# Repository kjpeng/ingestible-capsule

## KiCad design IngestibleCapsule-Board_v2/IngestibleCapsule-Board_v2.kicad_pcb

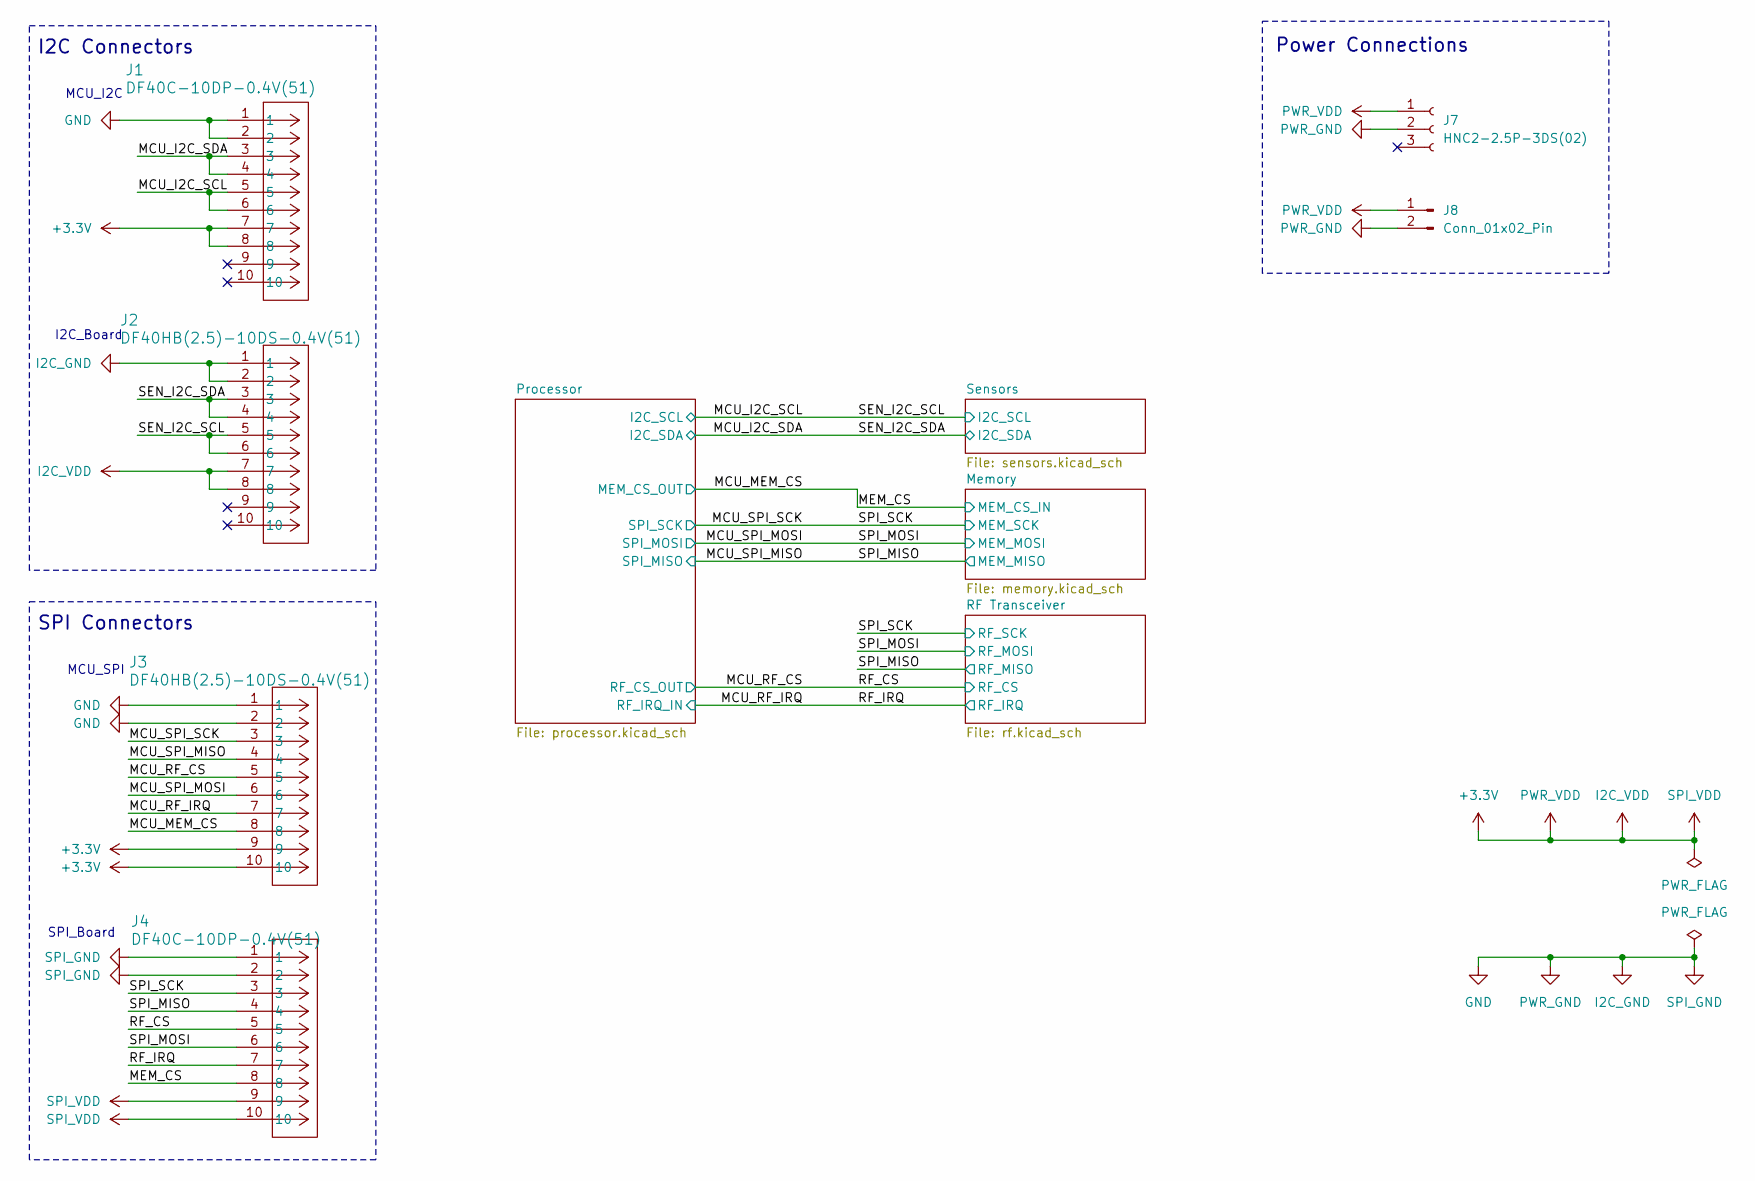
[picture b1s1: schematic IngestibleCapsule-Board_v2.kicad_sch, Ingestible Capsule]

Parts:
J1, J4: DF40C-10DP-0.4V(51)
J2, J3: DF40HB(2.5)-10DS-0.4V(51)
J7: HNC2-2.5P-3DS(02)
J8: Conn_01x02_Pin; PinSocket_1x02_P2.54mm_Vertical

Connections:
+3.3V: J1.7, J1.8, J2.7, J2.8, J3.9, J3.10, J4.9, J4.10, J7.1, J8.1; also elsewhere on the board
/MCU_I2C_SCL: J1.5, J1.6, J2.5, J2.6; also elsewhere on the board
/MCU_I2C_SDA: J1.3, J1.4, J2.3, J2.4; also elsewhere on the board
/MCU_MEM_CS: J3.8, J4.8; also elsewhere on the board
/MCU_RF_CS: J3.5, J4.5; also elsewhere on the board
/MCU_RF_IRQ: J3.7, J4.7; also elsewhere on the board
/MCU_SPI_MISO: J3.4, J4.4; also elsewhere on the board
/MCU_SPI_MOSI: J3.6, J4.6; also elsewhere on the board
/MCU_SPI_SCK: J3.3, J4.3; also elsewhere on the board
GND: J1.1, J1.2, J2.1, J2.2, J3.1, J3.2, J4.1, J4.2, J7.2, J8.2; also elsewhere on the board

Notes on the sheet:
MCU_I2C
I2C_Board
MCU_SPI
SPI_Board
SPI Connectors
I2C Connectors
Power Connections

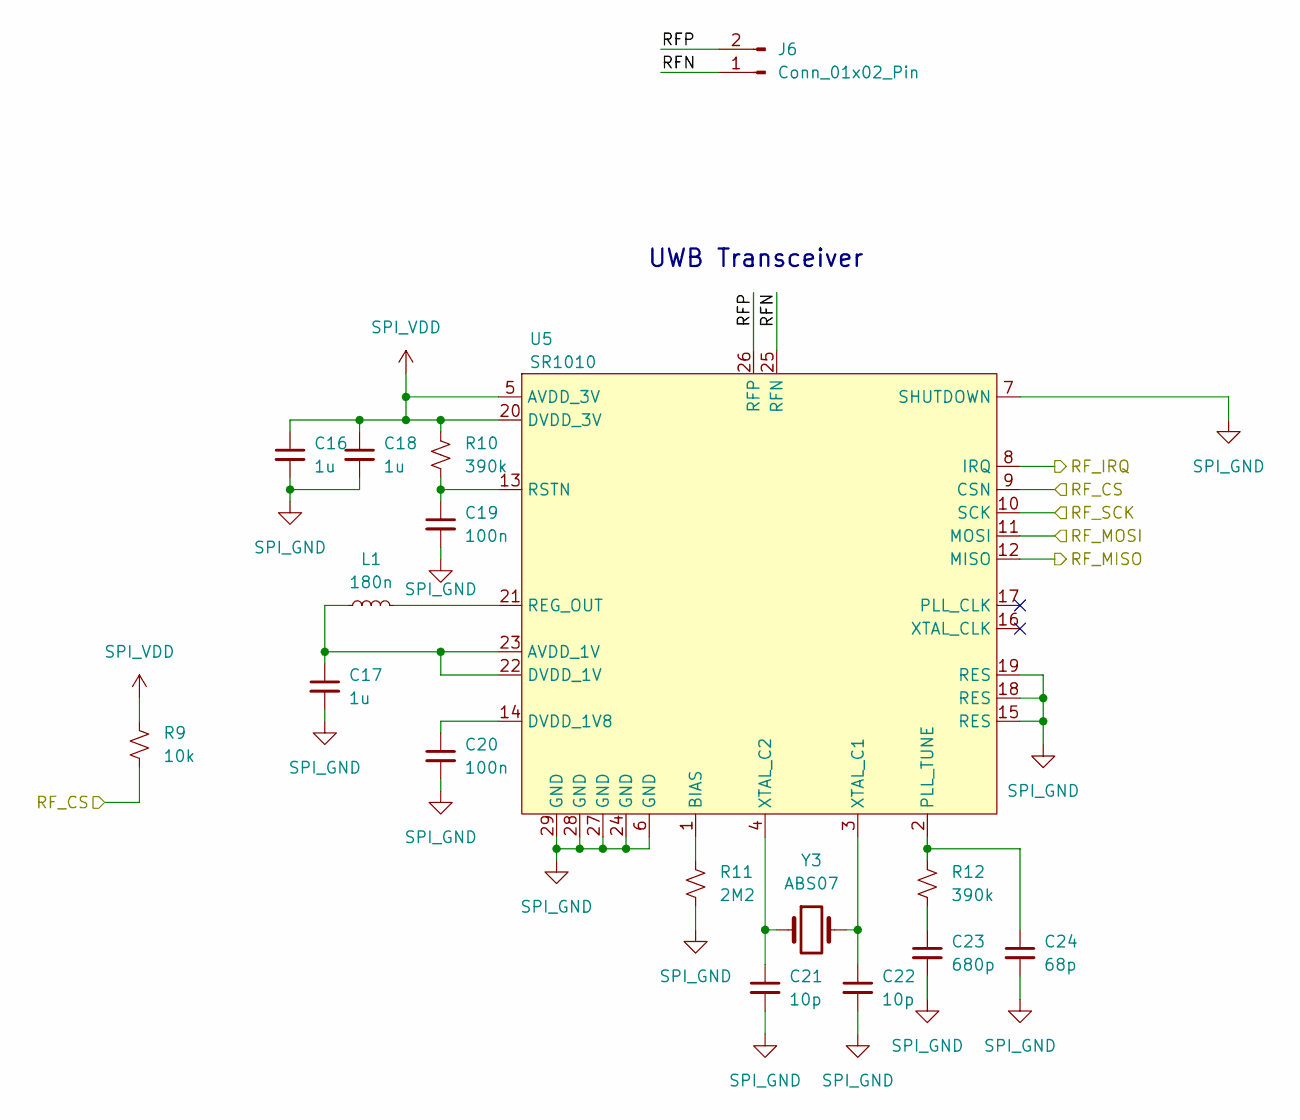
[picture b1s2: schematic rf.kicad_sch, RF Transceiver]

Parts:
C16, C17, C18: 1u; C_0402_1005Metric
C19, C20: 100n; C_0402_1005Metric
C21, C22: 10p; C_0402_1005Metric
C23: 680p; C_0402_1005Metric
C24: 68p; C_0402_1005Metric
J6: Conn_01x02_Pin; BM02BSRSSTBLFSN
L1: 180n; L_0402_1005Metric
R9: 10k; R_0402_1005Metric
R10, R12: 390k; R_0402_1005Metric
R11: 2M2; R_0603_1608Metric
U5: SR1010
Y3: ABS07; ABS07-120-32.768KHZ-T

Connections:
+3.3V: C16.1, C18.1, R9.1, R10.1, U5.5 (AVDD_3V), U5.20 (DVDD_3V); also elsewhere on the board
/MCU_RF_CS: R9.2, U5.9 (CSN); also elsewhere on the board
/MCU_RF_IRQ: U5.8 (IRQ); also elsewhere on the board
/MCU_SPI_MISO: U5.12 (MISO); also elsewhere on the board
/MCU_SPI_MOSI: U5.11 (MOSI); also elsewhere on the board
/MCU_SPI_SCK: U5.10 (SCK); also elsewhere on the board
/RF Transceiver/RFN: J6.1, U5.25 (RFN)
/RF Transceiver/RFP: J6.2, U5.26 (RFP)
GND: C16.2, C17.2, C18.2, C19.2, C20.2, C21.2, C22.2, C23.2, C24.2, R11.2, U5.6 (GND), U5.7 (SHUTDOWN), U5.15 (RES), U5.18 (RES), U5.19 (RES), U5.24 (GND), U5.27 (GND), U5.28 (GND), U5.29 (GND); also elsewhere on the board
unnamed: C23.1, R12.2
unnamed: C17.1, L1.1, U5.22 (DVDD_1V), U5.23 (AVDD_1V)
unnamed: R11.1, U5.1 (BIAS)
unnamed: C20.1, U5.14 (DVDD_1V8)
unnamed: C24.1, R12.1, U5.2 (PLL_TUNE)
unnamed: L1.2, U5.21 (REG_OUT)
unnamed: C19.1, R10.2, U5.13 (RSTN)
unnamed: C22.1, U5.3 (XTAL_C1), Y3.2
unnamed: C21.1, U5.4 (XTAL_C2), Y3.1

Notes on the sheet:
UWB Transceiver

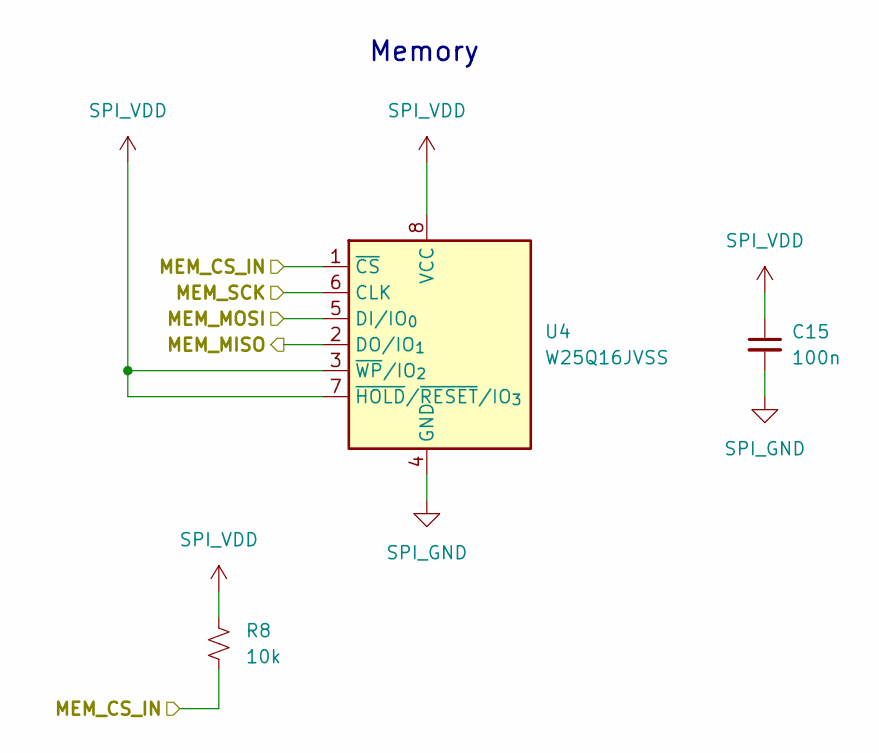
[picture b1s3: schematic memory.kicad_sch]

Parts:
C15: 100n; C_0402_1005Metric
R8: 10k; R_0402_1005Metric
U4: W25Q16JVSS; SOIC-8_5.3x5.3mm_P1.27mm

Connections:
+3.3V: C15.1, R8.1, U4.3 (~WP/IO_{2}), U4.7 (~HOLD/~RESET/IO_{3}), U4.8 (VCC); also elsewhere on the board
/MCU_MEM_CS: R8.2, U4.1 (~CS); also elsewhere on the board
/MCU_SPI_MISO: U4.2 (DO/IO_{1}); also elsewhere on the board
/MCU_SPI_MOSI: U4.5 (DI/IO_{0}); also elsewhere on the board
/MCU_SPI_SCK: U4.6 (CLK); also elsewhere on the board
GND: C15.2, U4.4 (GND); also elsewhere on the board

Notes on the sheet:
Memory

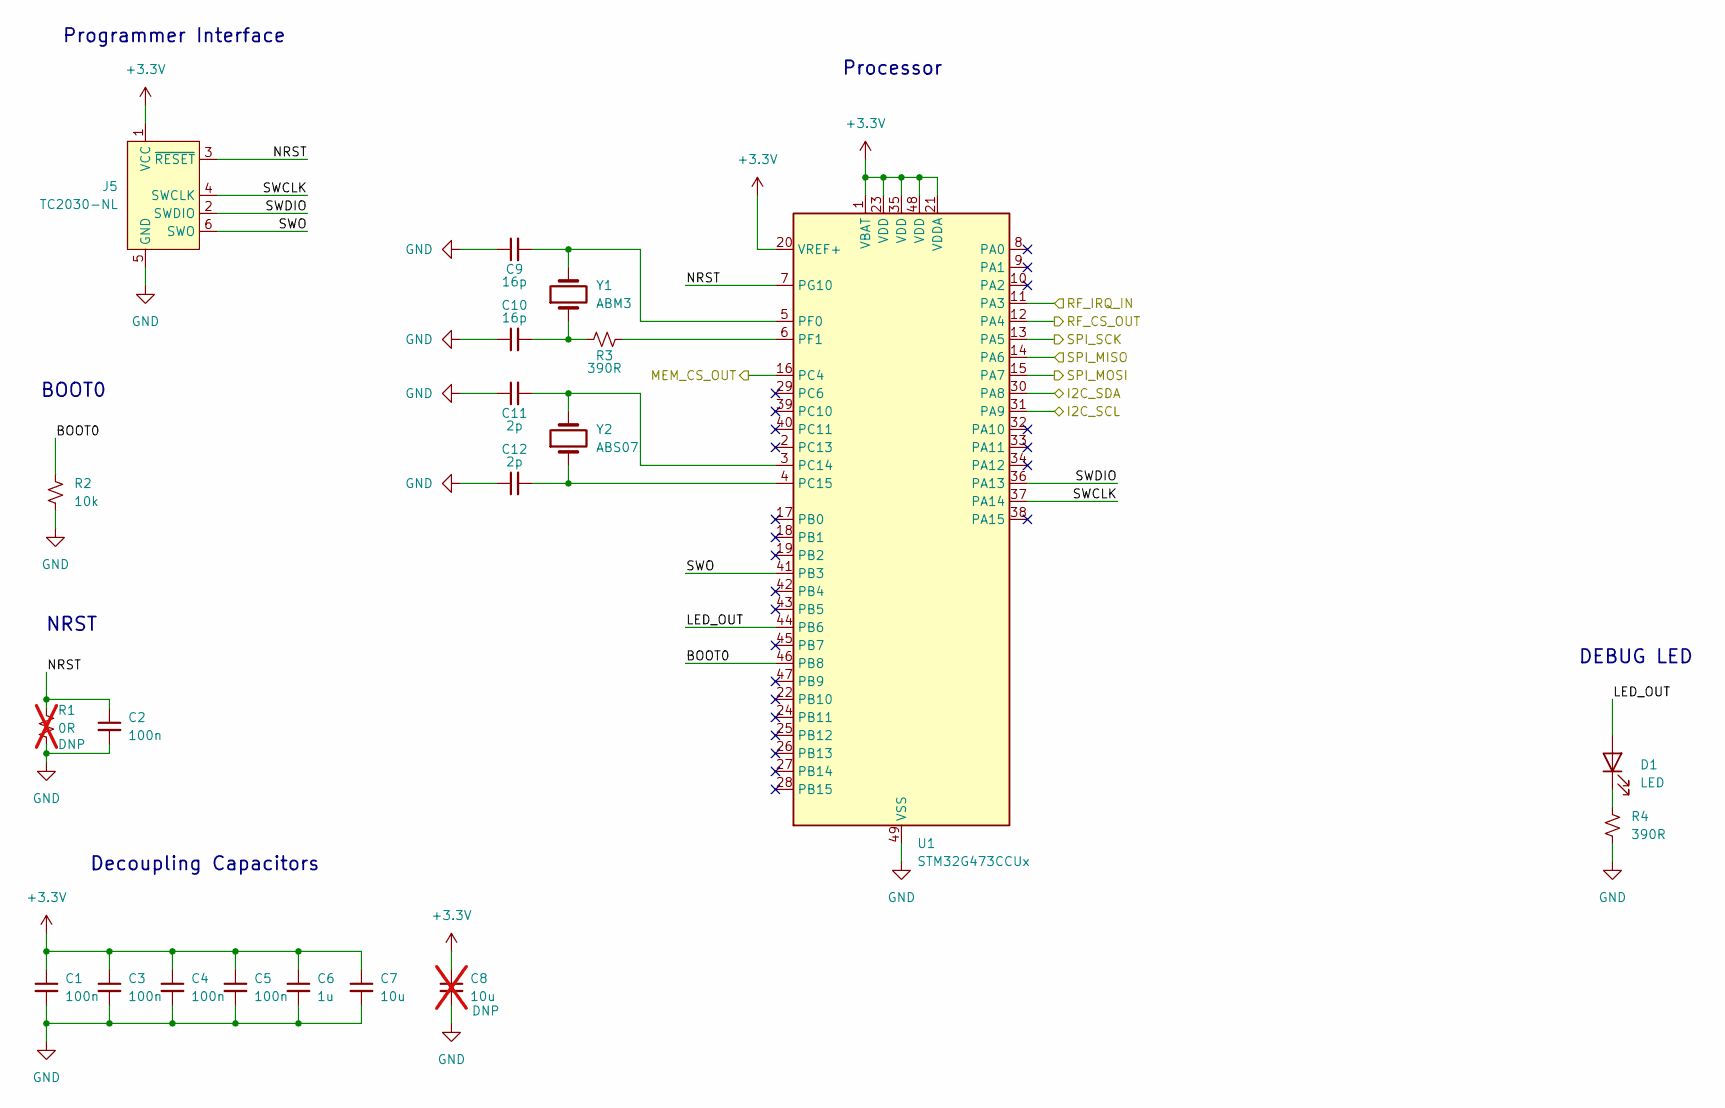
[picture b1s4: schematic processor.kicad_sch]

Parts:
C1, C2, C3, C4, C5: 100n; C_0402_1005Metric
C6: 1u; C_0402_1005Metric
C7: 10u; C_0603_1608Metric
C8: 10u; C_0603_1608Metric; not fitted
C9, C10: 16p; C_0402_1005Metric
C11, C12: 2p; C_0402_1005Metric
D1: LED; LED_0402_1005Metric
J5: TC2030-NL; Tag-Connect_TC2030-IDC-NL_2x03_P1.27mm_Vertical
R1: 0R; R_0402_1005Metric; not fitted
R2: 10k; R_0402_1005Metric
R3, R4: 390R; R_0402_1005Metric
U1: STM32G473CCUx; QFN-48-1EP_7x7mm_P0.5mm_EP5.6x5.6mm
Y1: ABM3; ABM3-48.000MHZ-B2-T
Y2: ABS07; ABS07-120-32.768KHZ-T

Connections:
+3.3V: C1.1, C3.1, C4.1, C5.1, C6.1, C7.1, C8.1, J5.1 (VCC), U1.1 (VBAT), U1.20 (VREF+), U1.21 (VDDA), U1.23 (VDD), U1.35 (VDD), U1.48 (VDD); also elsewhere on the board
/MCU_I2C_SCL: U1.31 (PA9); also elsewhere on the board
/MCU_I2C_SDA: U1.30 (PA8); also elsewhere on the board
/MCU_MEM_CS: U1.16 (PC4); also elsewhere on the board
/MCU_RF_CS: U1.12 (PA4); also elsewhere on the board
/MCU_RF_IRQ: U1.11 (PA3); also elsewhere on the board
/MCU_SPI_MISO: U1.14 (PA6); also elsewhere on the board
/MCU_SPI_MOSI: U1.15 (PA7); also elsewhere on the board
/MCU_SPI_SCK: U1.13 (PA5); also elsewhere on the board
/Processor/BOOT0: R2.1, U1.46 (PB8)
/Processor/LED_OUT: D1.2 (A), U1.44 (PB6)
/Processor/NRST: C2.1, J5.3 (~RESET), R1.1, U1.7 (PG10)
/Processor/SWCLK: J5.4 (SWCLK), U1.37 (PA14)
/Processor/SWDIO: J5.2 (SWDIO), U1.36 (PA13)
/Processor/SWO: J5.6 (SWO), U1.41 (PB3)
GND: C1.2, C2.2, C3.2, C4.2, C5.2, C6.2, C7.2, C8.2, C9.1, C10.1, C11.1, C12.1, J5.5 (GND), R1.2, R2.2, R4.2, U1.49 (VSS); also elsewhere on the board
unnamed: C10.2, R3.1, Y1.1
unnamed: D1.1 (K), R4.1
unnamed: C11.2, U1.3 (PC14), Y2.2
unnamed: C12.2, U1.4 (PC15), Y2.1
unnamed: C9.2, U1.5 (PF0), Y1.2
unnamed: R3.2, U1.6 (PF1)

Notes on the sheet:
Programmer Interface
Decoupling Capacitors
BOOT0
NRST
Processor
DEBUG LED

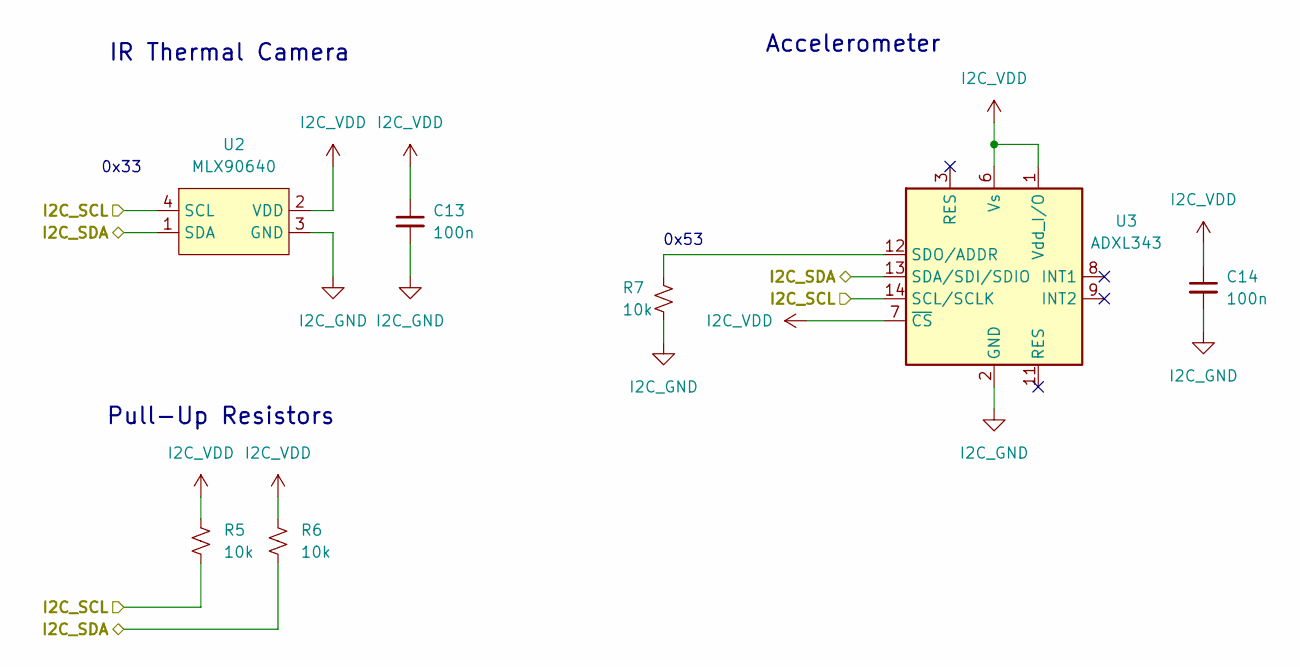
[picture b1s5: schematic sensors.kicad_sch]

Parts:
C13, C14: 100n; C_0402_1005Metric
R5, R6, R7: 10k; R_0402_1005Metric
U2: MLX90640
U3: ADXL343; LGA-14_3x5mm_P0.8mm_LayoutBorder1x6y

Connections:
+3.3V: C13.1, C14.1, R5.1, R6.1, U2.2 (VDD), U3.1 (Vdd_I/O), U3.6 (Vs), U3.7 (~CS); also elsewhere on the board
/MCU_I2C_SCL: R5.2, U2.4 (SCL), U3.14 (SCL/SCLK); also elsewhere on the board
/MCU_I2C_SDA: R6.2, U2.1 (SDA), U3.13 (SDA/SDI/SDIO); also elsewhere on the board
GND: C13.2, C14.2, R7.1, U2.3 (GND), U3.2 (GND), U3.4 (GND), U3.5 (GND); also elsewhere on the board
unnamed: R7.2, U3.12 (SDO/ADDR)

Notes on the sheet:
0x53
IR Thermal Camera
Accelerometer
0x33
Pull-Up Resistors

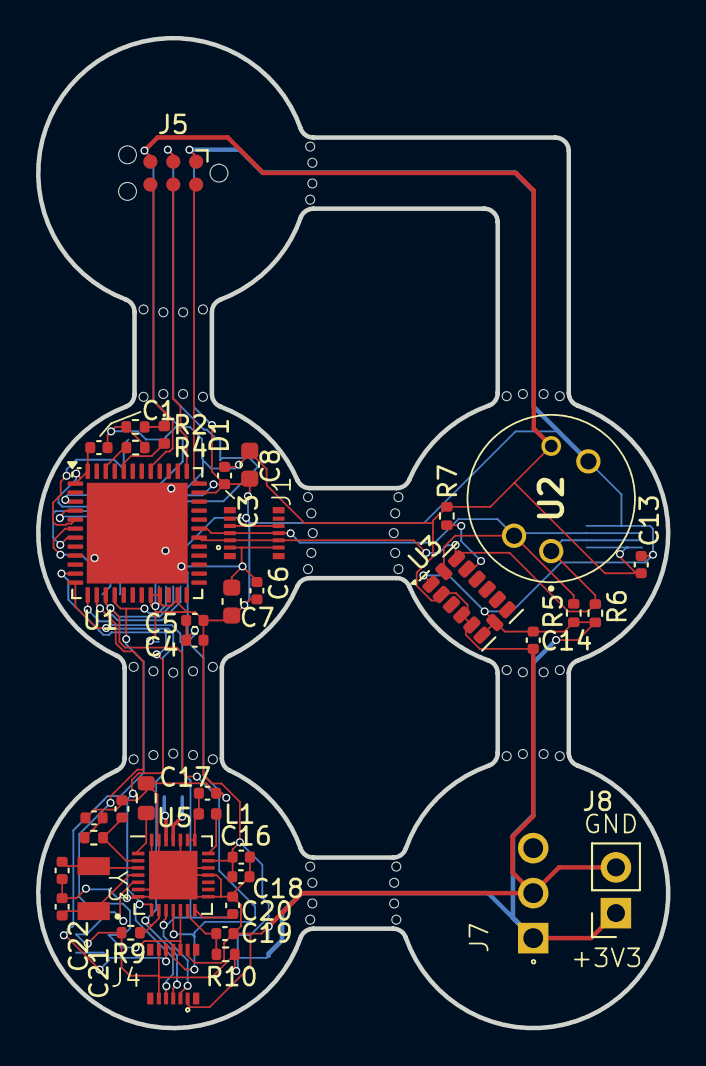
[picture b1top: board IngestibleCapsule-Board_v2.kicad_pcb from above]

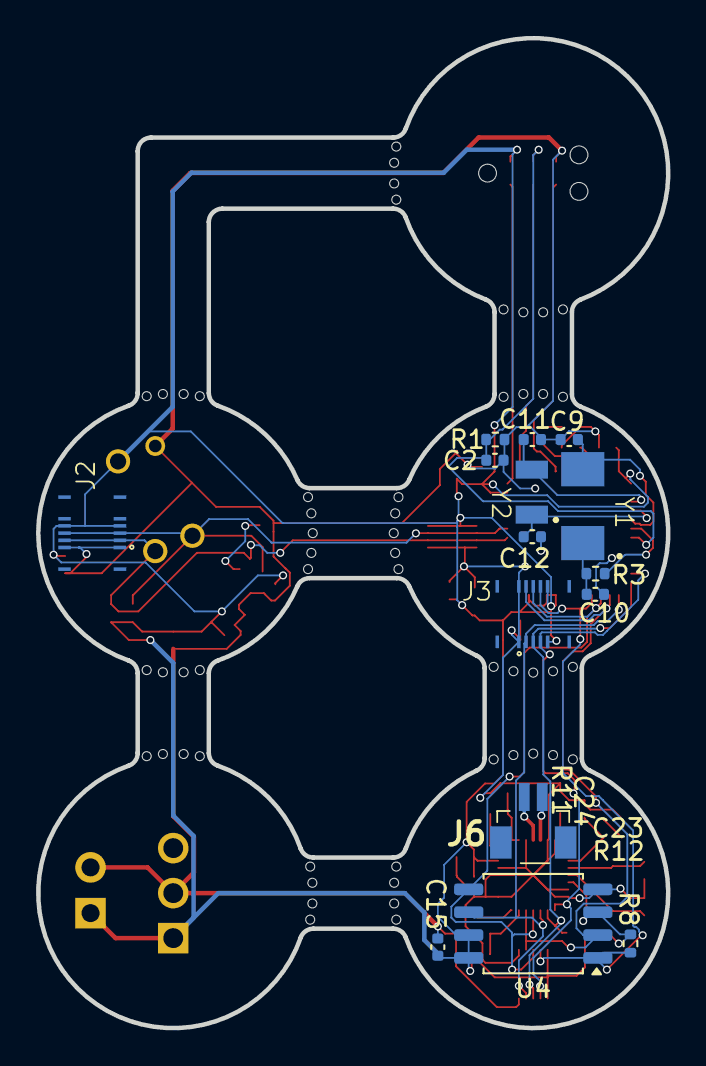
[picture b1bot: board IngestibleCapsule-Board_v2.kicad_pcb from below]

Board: 2 copper layers, 35.0 x 55.0 mm, 66 parts (15 on the bottom side), 34 nets.

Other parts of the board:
i2c_2_2, i2c_2_2#2: VAL**; i2c_2_2
prog_3_2, prog_3_2#2: VAL**; prog_3_2
pwr_4_2, pwr_4_2#2, pwr_4_2#3, pwr_4_2#4, pwr_4_2#5, pwr_4_2#6: VAL**; pwr_4_2
spi_4_2, spi_4_2#2: VAL**; spi_4_2

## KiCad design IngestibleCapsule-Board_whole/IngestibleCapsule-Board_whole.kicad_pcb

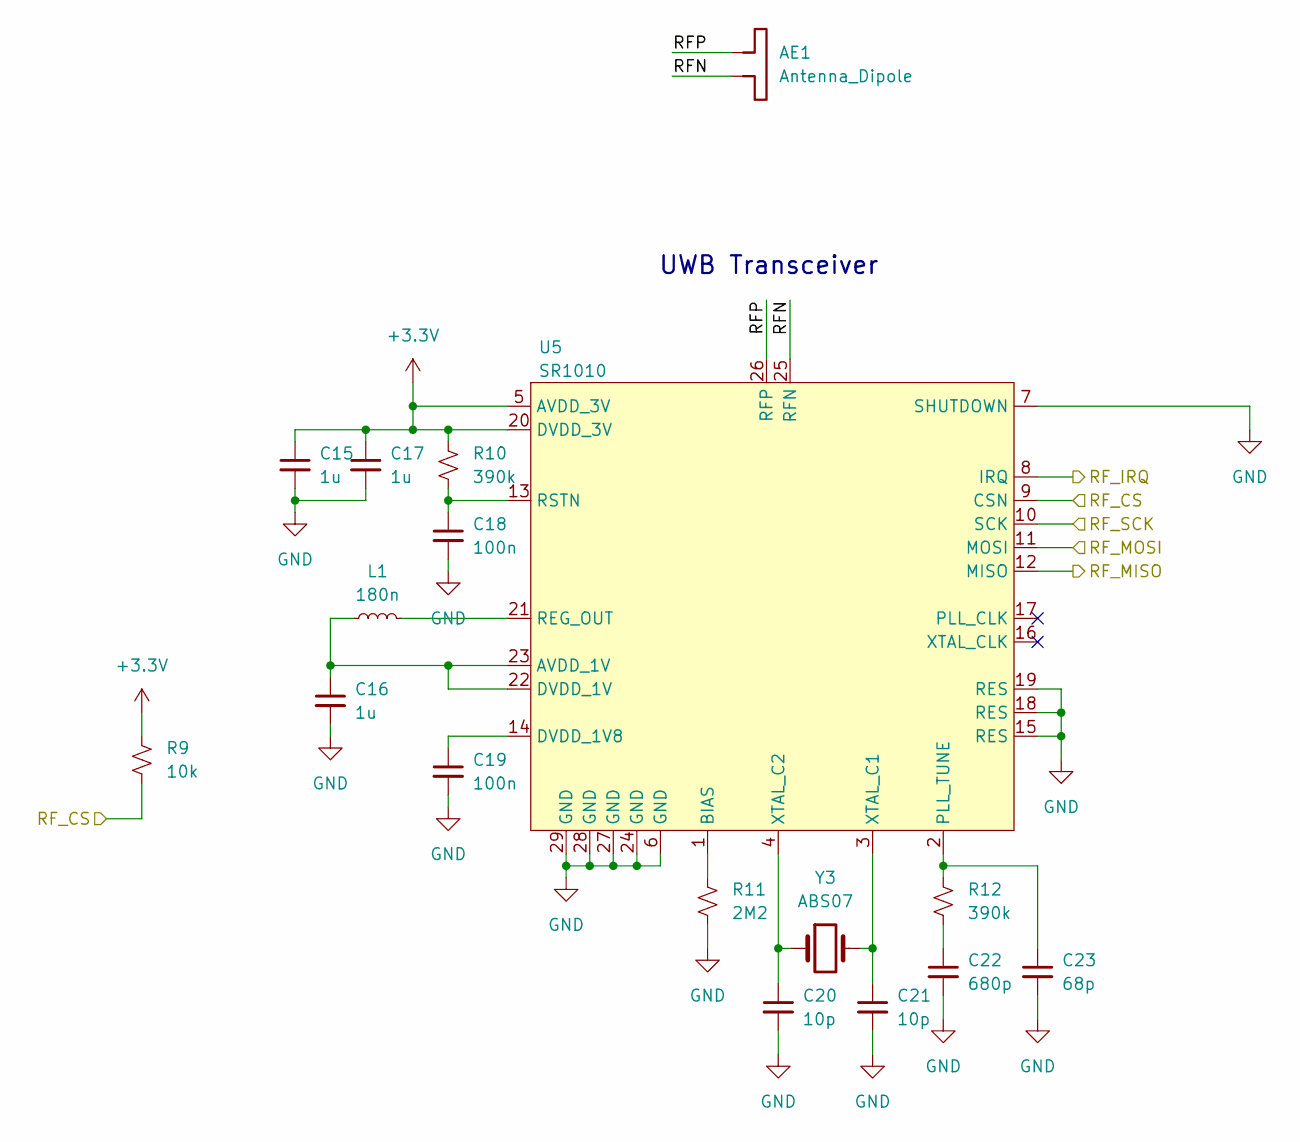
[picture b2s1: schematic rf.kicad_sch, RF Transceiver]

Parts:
AE1: Antenna_Dipole; Dipole Antenna
C15, C16, C17: 1u; C_0402_1005Metric
C18, C19: 100n; C_0402_1005Metric
C20, C21: 10p; C_0402_1005Metric
C22: 680p; C_0402_1005Metric
C23: 68p; C_0402_1005Metric
L1: 180n; L_0402_1005Metric
R9: 10k; R_0402_1005Metric
R10, R12: 390k; R_0402_1005Metric
R11: 2M2; R_0603_1608Metric
U5: SR1010; QFN-28-1EP_4x4mm_P0.4mm_EP2.7x2.7mm
Y3: ABS07; ABS07-120-32.768KHZ-T

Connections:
+3.3V: C15.1, C17.1, R9.1, R10.1, U5.5 (AVDD_3V), U5.20 (DVDD_3V); also elsewhere on the board
/Memory/MEM_MISO: U5.12 (MISO); also elsewhere on the board
/Memory/MEM_MOSI: U5.11 (MOSI); also elsewhere on the board
/Memory/MEM_SCK: U5.10 (SCK); also elsewhere on the board
/Processor/RF_CS_OUT: R9.2, U5.9 (CSN); also elsewhere on the board
/Processor/RF_IRQ_IN: U5.8 (IRQ); also elsewhere on the board
/RF Transceiver/RFN: AE1.2, U5.25 (RFN)
/RF Transceiver/RFP: AE1.1, U5.26 (RFP)
GND: C15.2, C16.2, C17.2, C18.2, C19.2, C20.2, C21.2, C22.2, C23.2, R11.2, U5.6 (GND), U5.7 (SHUTDOWN), U5.15 (RES), U5.18 (RES), U5.19 (RES), U5.24 (GND), U5.27 (GND), U5.28 (GND), U5.29 (GND); also elsewhere on the board
unnamed: C22.1, R12.2
unnamed: C16.1, L1.1, U5.22 (DVDD_1V), U5.23 (AVDD_1V)
unnamed: R11.1, U5.1 (BIAS)
unnamed: C19.1, U5.14 (DVDD_1V8)
unnamed: C23.1, R12.1, U5.2 (PLL_TUNE)
unnamed: L1.2, U5.21 (REG_OUT)
unnamed: C18.1, R10.2, U5.13 (RSTN)
unnamed: C21.1, U5.3 (XTAL_C1), Y3.2
unnamed: C20.1, U5.4 (XTAL_C2), Y3.1

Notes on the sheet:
UWB Transceiver

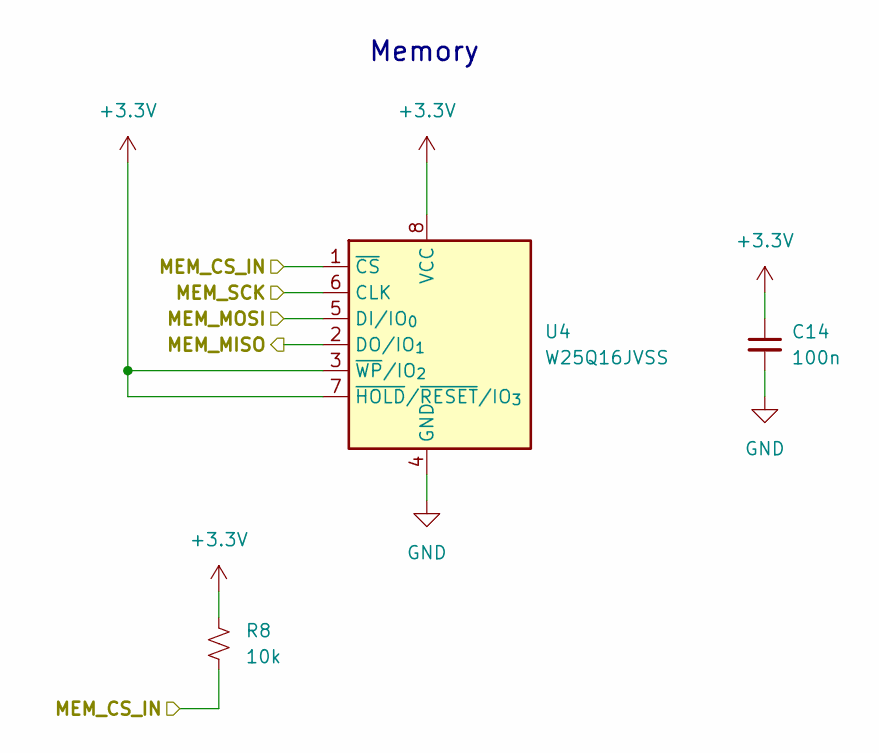
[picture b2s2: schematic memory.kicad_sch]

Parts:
C14: 100n; C_0402_1005Metric
R8: 10k; R_0402_1005Metric
U4: W25Q16JVSS; SOIC-8_5.3x5.3mm_P1.27mm

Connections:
+3.3V: C14.1, R8.1, U4.3 (~WP/IO_{2}), U4.7 (~HOLD/~RESET/IO_{3}), U4.8 (VCC); also elsewhere on the board
/Memory/MEM_CS_IN: R8.2, U4.1 (~CS); also elsewhere on the board
/Memory/MEM_MISO: U4.2 (DO/IO_{1}); also elsewhere on the board
/Memory/MEM_MOSI: U4.5 (DI/IO_{0}); also elsewhere on the board
/Memory/MEM_SCK: U4.6 (CLK); also elsewhere on the board
GND: C14.2, U4.4 (GND); also elsewhere on the board

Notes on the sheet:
Memory

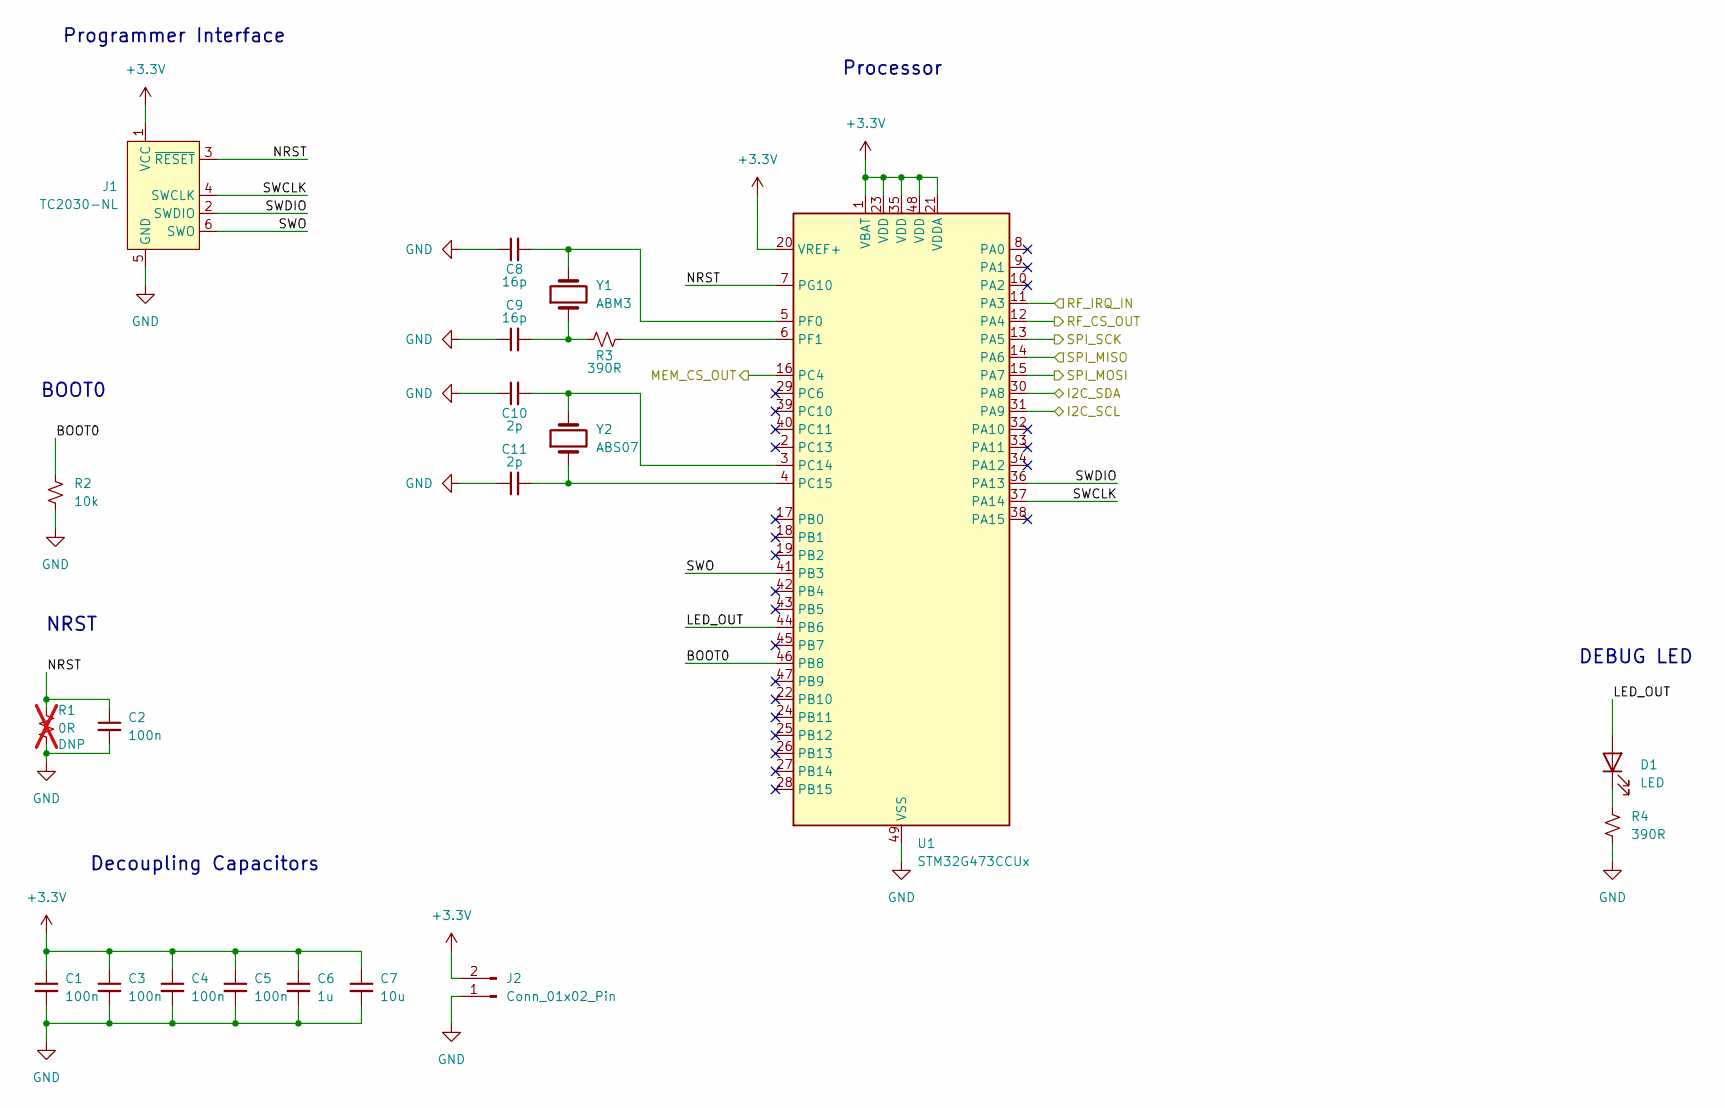
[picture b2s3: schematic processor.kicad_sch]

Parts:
C1, C2, C3, C4, C5: 100n; C_0402_1005Metric
C6: 1u; C_0402_1005Metric
C7: 10u; C_0603_1608Metric
C8, C9: 16p; C_0402_1005Metric
C10, C11: 2p; C_0402_1005Metric
D1: LED; LED_0402_1005Metric
J1: TC2030-NL; Tag-Connect_TC2030-IDC-NL_2x03_P1.27mm_Vertical
J2: Conn_01x02_Pin; PinHeader_1x02_P2.54mm_Vertical
R1: 0R; R_0402_1005Metric; not fitted
R2: 10k; R_0402_1005Metric
R3, R4: 390R; R_0402_1005Metric
U1: STM32G473CCUx; QFN-48-1EP_7x7mm_P0.5mm_EP5.6x5.6mm
Y1: ABM3; ABM3-48.000MHZ-B2-T
Y2: ABS07; ABS07-120-32.768KHZ-T

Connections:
+3.3V: C1.1, C3.1, C4.1, C5.1, C6.1, C7.1, J1.1 (VCC), J2.2, U1.1 (VBAT), U1.20 (VREF+), U1.21 (VDDA), U1.23 (VDD), U1.35 (VDD), U1.48 (VDD); also elsewhere on the board
/Memory/MEM_CS_IN: U1.16 (PC4); also elsewhere on the board
/Memory/MEM_MISO: U1.14 (PA6); also elsewhere on the board
/Memory/MEM_MOSI: U1.15 (PA7); also elsewhere on the board
/Memory/MEM_SCK: U1.13 (PA5); also elsewhere on the board
/Processor/BOOT0: R2.1, U1.46 (PB8)
/Processor/I2C_SCL: U1.31 (PA9); also elsewhere on the board
/Processor/I2C_SDA: U1.30 (PA8); also elsewhere on the board
/Processor/LED_OUT: D1.2 (A), U1.44 (PB6)
/Processor/NRST: C2.1, J1.3 (~RESET), R1.1, U1.7 (PG10)
/Processor/RF_CS_OUT: U1.12 (PA4); also elsewhere on the board
/Processor/RF_IRQ_IN: U1.11 (PA3); also elsewhere on the board
/Processor/SWCLK: J1.4 (SWCLK), U1.37 (PA14)
/Processor/SWDIO: J1.2 (SWDIO), U1.36 (PA13)
/Processor/SWO: J1.6 (SWO), U1.41 (PB3)
GND: C1.2, C2.2, C3.2, C4.2, C5.2, C6.2, C7.2, C8.1, C9.1, C10.1, C11.1, J1.5 (GND), J2.1, R1.2, R2.2, R4.2, U1.49 (VSS); also elsewhere on the board
unnamed: C9.2, R3.1, Y1.1
unnamed: D1.1 (K), R4.1
unnamed: C10.2, U1.3 (PC14), Y2.2
unnamed: C11.2, U1.4 (PC15), Y2.1
unnamed: C8.2, U1.5 (PF0), Y1.2
unnamed: R3.2, U1.6 (PF1)

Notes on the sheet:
Programmer Interface
Decoupling Capacitors
BOOT0
NRST
Processor
DEBUG LED

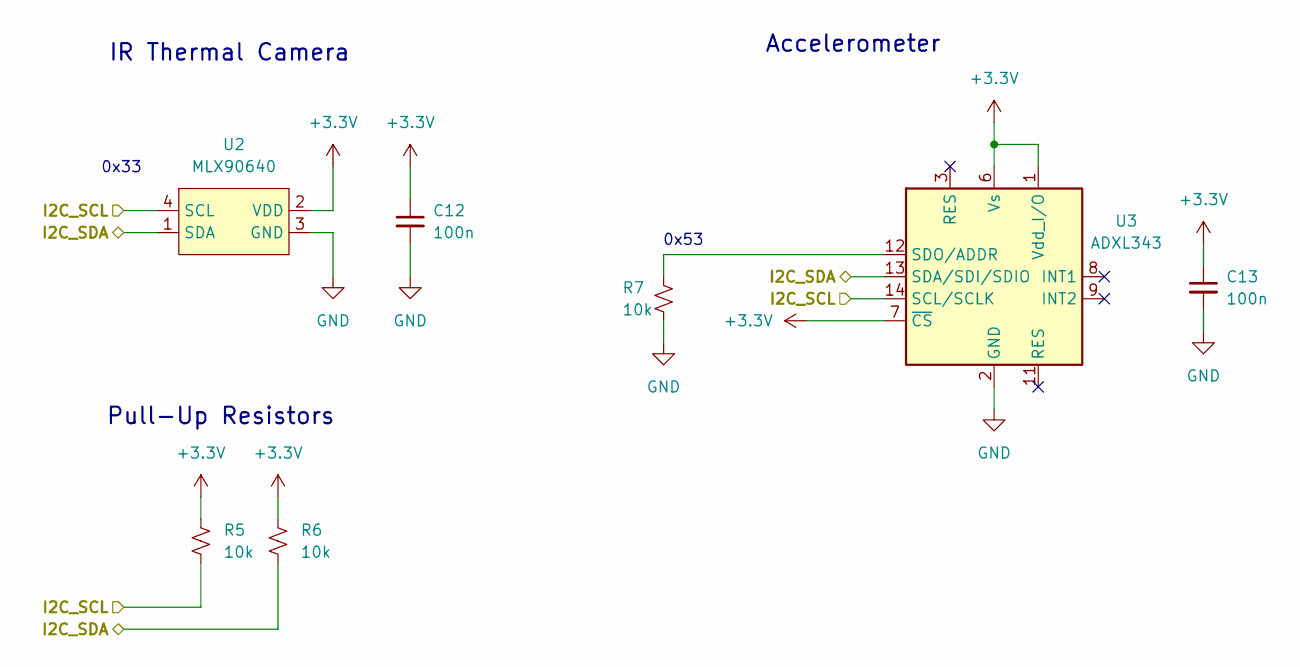
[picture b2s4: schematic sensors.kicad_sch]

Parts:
C12, C13: 100n; C_0402_1005Metric
R5, R6, R7: 10k; R_0402_1005Metric
U2: MLX90640
U3: ADXL343; LGA-14_3x5mm_P0.8mm_LayoutBorder1x6y

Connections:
+3.3V: C12.1, C13.1, R5.1, R6.1, U2.2 (VDD), U3.1 (Vdd_I/O), U3.6 (Vs), U3.7 (~CS); also elsewhere on the board
/Processor/I2C_SCL: R5.2, U2.4 (SCL), U3.14 (SCL/SCLK); also elsewhere on the board
/Processor/I2C_SDA: R6.2, U2.1 (SDA), U3.13 (SDA/SDI/SDIO); also elsewhere on the board
GND: C12.2, C13.2, R7.1, U2.3 (GND), U3.2 (GND), U3.4 (GND), U3.5 (GND); also elsewhere on the board
unnamed: R7.2, U3.12 (SDO/ADDR)

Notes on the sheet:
0x53
IR Thermal Camera
Accelerometer
0x33
Pull-Up Resistors

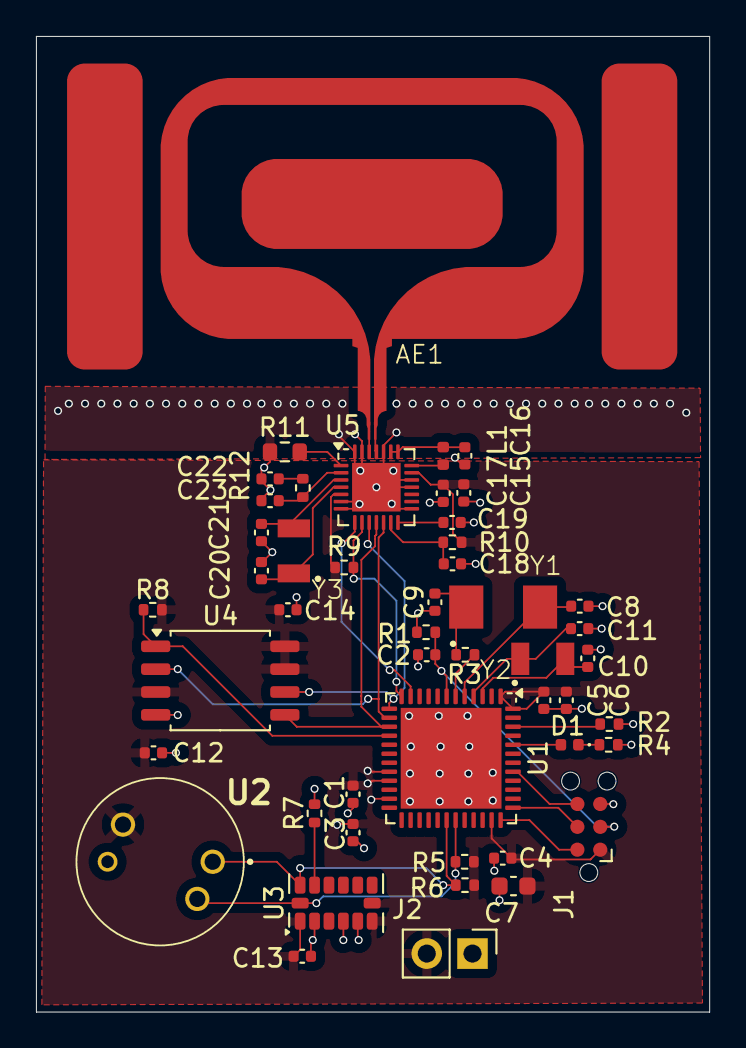
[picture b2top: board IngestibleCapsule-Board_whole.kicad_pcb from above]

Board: 2 copper layers, 37.4 x 54.2 mm, 48 parts (0 on the bottom side), 34 nets.

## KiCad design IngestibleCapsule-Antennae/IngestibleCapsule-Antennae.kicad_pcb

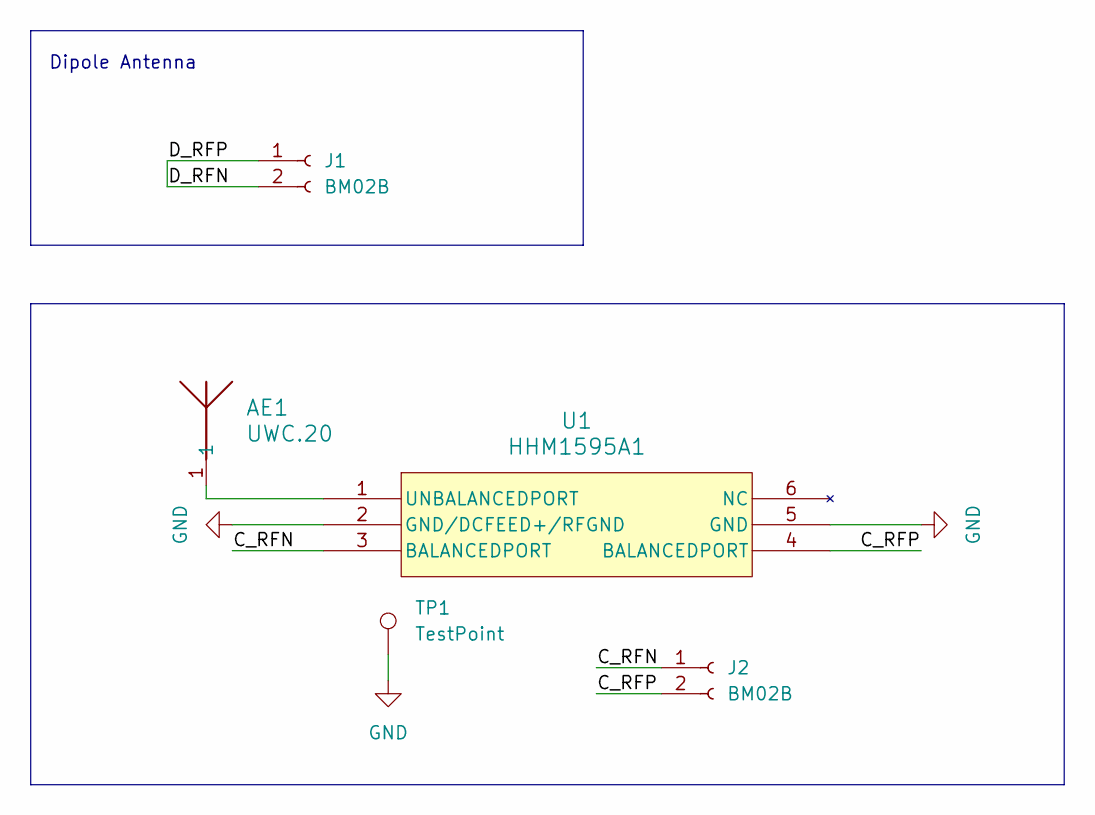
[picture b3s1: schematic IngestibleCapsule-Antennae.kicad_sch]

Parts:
AE1: UWC.20; ANT_SMD6_UWC_TAL
J1, J2: BM02B; BM02BSRSSTBLFSN
TP1: TestPoint; TestPoint_Pad_2.0x2.0mm
U1: HHM1595A1; HHM-6_2P0X1P25

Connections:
/C_RFN: J2.1, U1.3 (BALANCEDPORT)
/C_RFP: J2.2, U1.4 (BALANCEDPORT)
/D_RFN: J1.1, J1.2
GND: TP1.1, U1.2 (GND/DCFEED+/RFGND), U1.5 (GND)
unnamed: AE1.1, U1.1 (UNBALANCEDPORT)

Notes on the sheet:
Dipole Antenna

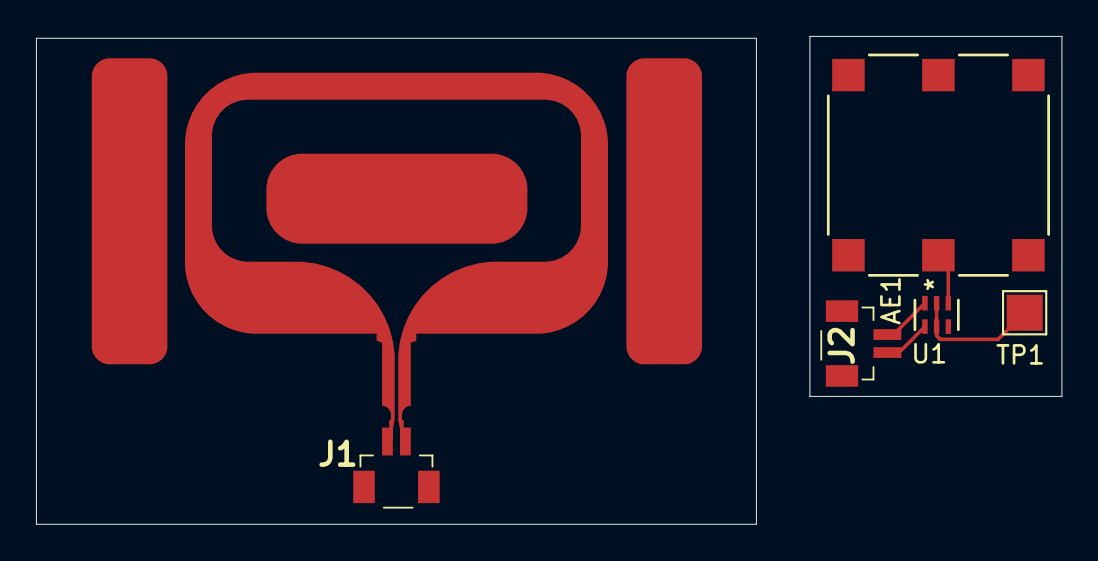
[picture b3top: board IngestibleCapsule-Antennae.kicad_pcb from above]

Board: 2 copper layers, 57.0 x 27.1 mm, 5 parts (0 on the bottom side), 5 nets.

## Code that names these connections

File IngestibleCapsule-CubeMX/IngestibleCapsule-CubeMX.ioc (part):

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Mcu.Name=STM32G473C(B-C-E)Ux
Mcu.Package=UFQFPN48
Mcu.UserName=STM32G473CCUx
PA11.Signal=GPIO_Input
PA13.Mode=Trace_Asynchronous_SW
PA13.Signal=SYS_JTMS-SWDIO
PA14.Mode=Trace_Asynchronous_SW
PA14.Signal=SYS_JTCK-SWCLK
PA3.GPIOParameters=GPIO_Label
PA3.GPIO_Label=RF_IRQ_IN
PA3.Signal=GPIO_Input
PA4.GPIOParameters=GPIO_Label
PA4.GPIO_Label=RF_CS_OUT
PA4.Signal=GPIO_Output
PA5.Mode=Full_Duplex_Master
PA5.Signal=SPI1_SCK
PA6.Mode=Full_Duplex_Master
PA6.Signal=SPI1_MISO
PA7.Mode=Full_Duplex_Master
PA7.Signal=SPI1_MOSI
PA8.Mode=I2C
PA8.Signal=I2C2_SDA
PA9.Mode=I2C
PA9.Signal=I2C2_SCL
PB10.Signal=GPIO_Input
PB3.Mode=Trace_Asynchronous_SW
PB3.Signal=SYS_JTDO-SWO
PB6.GPIOParameters=GPIO_Label
PB6.GPIO_Label=LED_OUT
PB6.Signal=GPIO_Output
PB9.Signal=GPIO_Input
PC14-OSC32_IN.Mode=LSE-External-Oscillator
PC14-OSC32_IN.Signal=RCC_OSC32_IN
PC15-OSC32_OUT.Mode=LSE-External-Oscillator
PC15-OSC32_OUT.Signal=RCC_OSC32_OUT
PC4.GPIOParameters=GPIO_Label
PC4.GPIO_Label=MEM_CS_OUT
PC4.Signal=GPIO_Output
PF0-OSC_IN.Mode=HSE-External-Oscillator
PF0-OSC_IN.Signal=RCC_OSC_IN
PF1-OSC_OUT.Mode=HSE-External-Oscillator
PF1-OSC_OUT.Signal=RCC_OSC_OUT
RCC.HSE_VALUE=8000000
RCC.SYSCLKFreq_VALUE=16000000
board=custom

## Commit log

2025-03-13 Initialize repo; first instance of full PCB
2025-03-13 larger vias implemented
2025-03-14 more gerbers
2025-04-01 beginning a whole board
2025-04-05 whole board
2025-04-07 larger_vias fix
2025-04-07 finally
2025-04-08 cubeide
2025-04-11 v2 drawing
2025-04-11 restarting pcb2
2025-04-11 updated drawing
2025-04-11 new drawing
2025-04-11 full v2 implementation, has 5 circles connected by mousebites
2025-04-24 fixed spi connector orientation
